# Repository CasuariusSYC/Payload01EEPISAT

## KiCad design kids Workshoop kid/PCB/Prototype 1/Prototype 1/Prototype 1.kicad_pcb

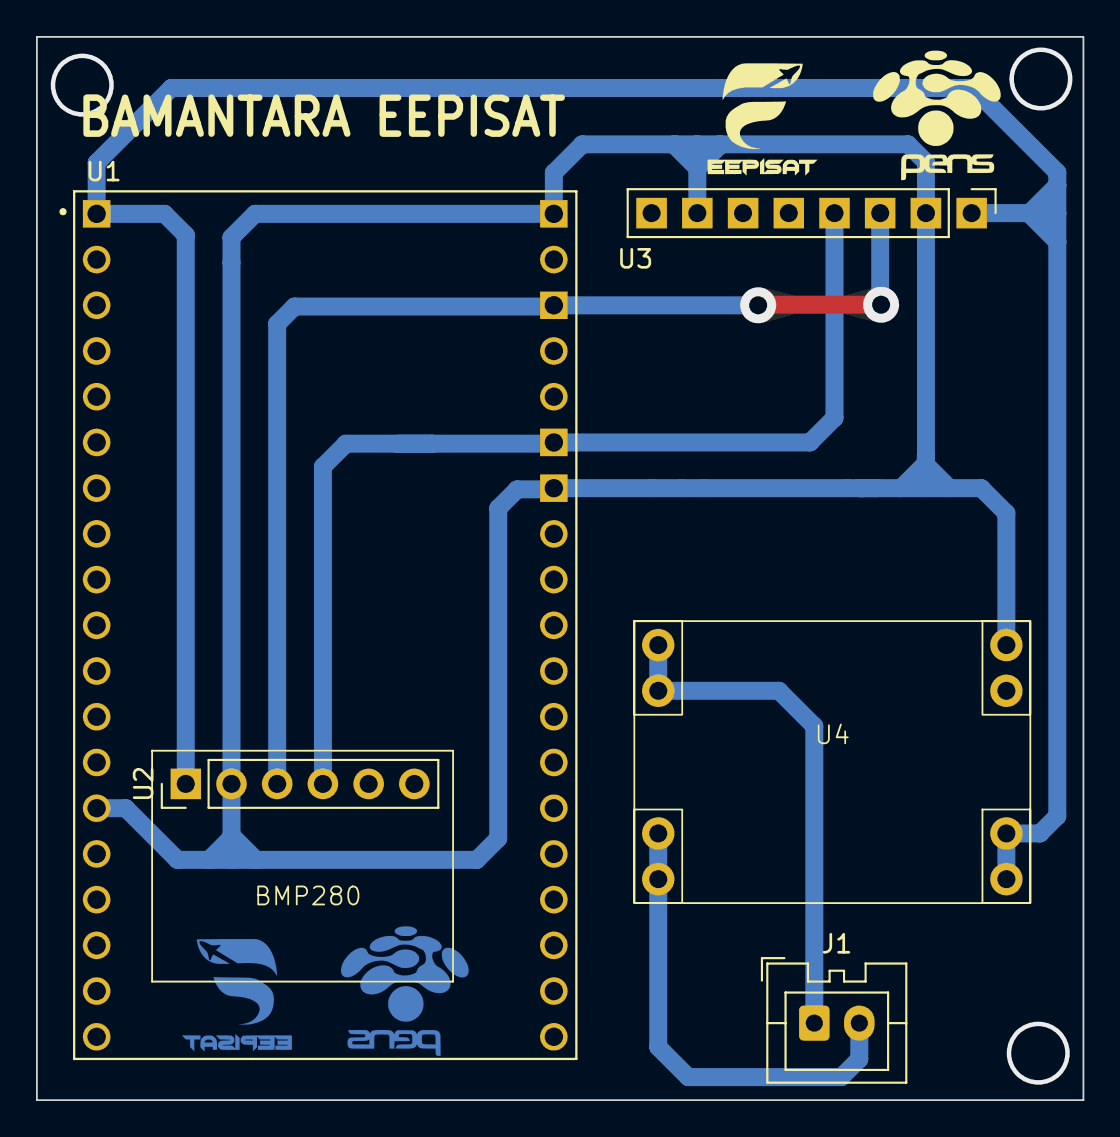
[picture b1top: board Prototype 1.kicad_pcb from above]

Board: 2 copper layers, 58.1 x 59.1 mm, 5 parts (0 on the bottom side), 6 nets.

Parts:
J1: Conn_01x02_Pin; JST_XA_B02B-XASK-1_1x02_P2.50mm_Vertical
U1: ESP32-DEVKITC-32U; MODULE_ESP32-DEVKITC-32U
U2: PinHeader_1x06_P2.54mm_Vertical
U3: PinHeader_1x08_P2.54mm_Vertical
U4: MP1584

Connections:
GND: U1.14 (GND1), U1.32 (GND2), U1.38 (GND3), U2.2 (GND), U3.2 (GND), U3.7 (AD0), U4.4 (OUT-)
unnamed: J1.1, U4.2 (IN-)
unnamed: J1.2, U4.1 (IN+)
SCL: U1.36 (IO22), U2.3 (SCL), U3.3 (SCL)
SDA: U1.33 (IO21), U2.4 (SDA), U3.4 (SDA)
VCC: U1.1 (3V3), U2.1 (VCC), U3.1 (VCC), U4.3 (OUT+)

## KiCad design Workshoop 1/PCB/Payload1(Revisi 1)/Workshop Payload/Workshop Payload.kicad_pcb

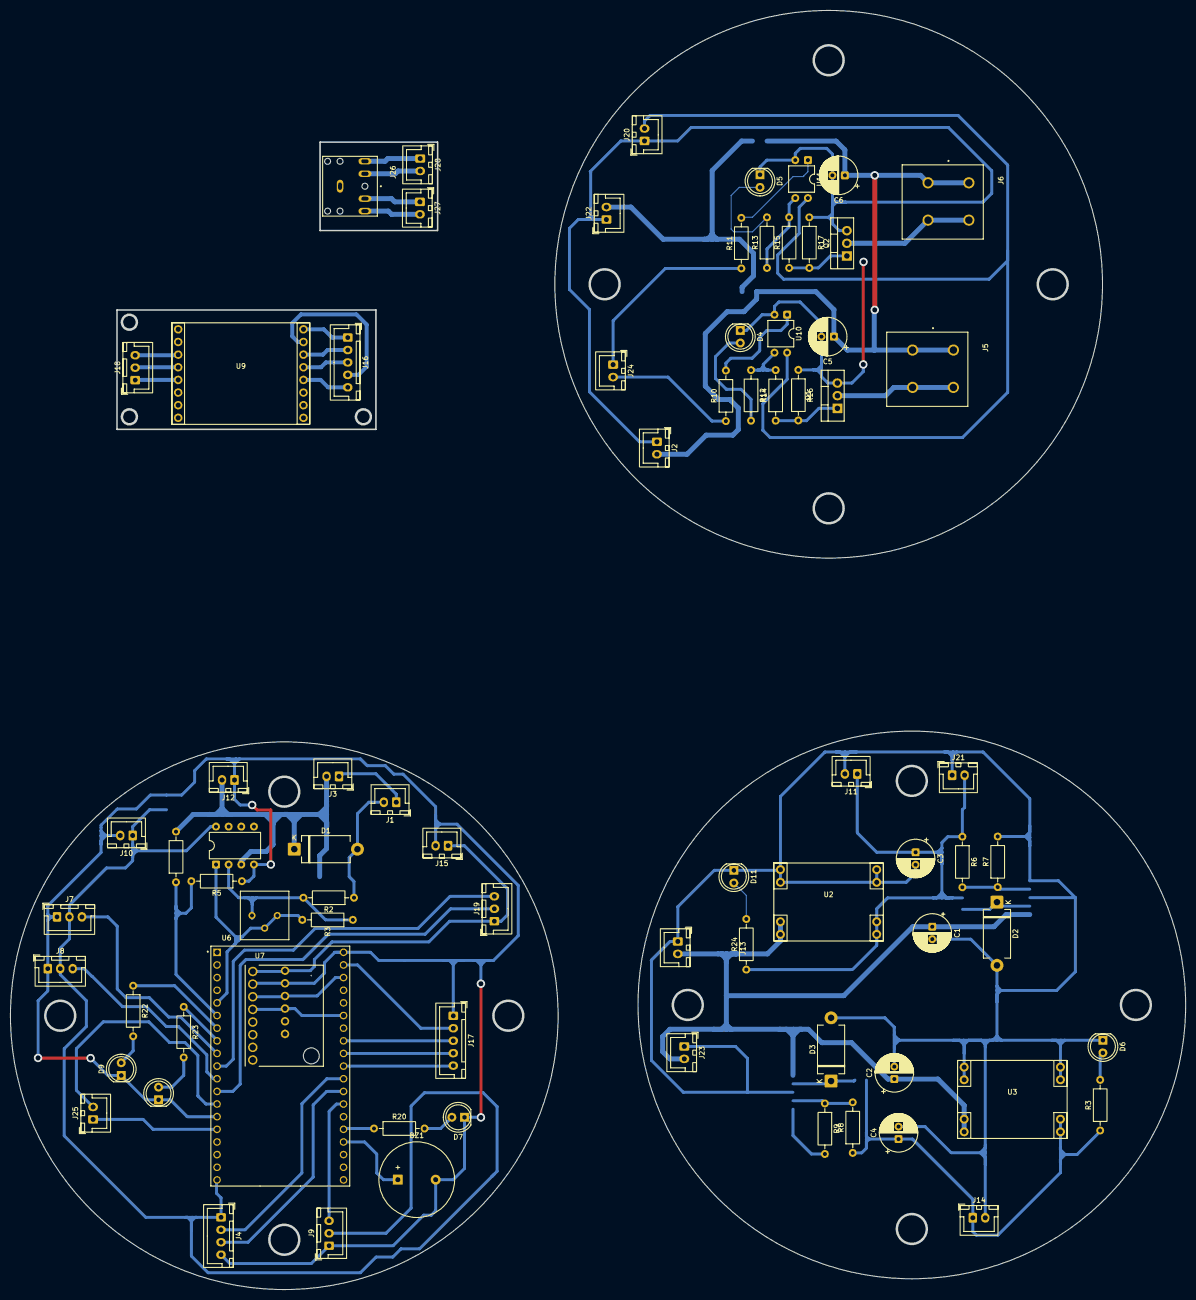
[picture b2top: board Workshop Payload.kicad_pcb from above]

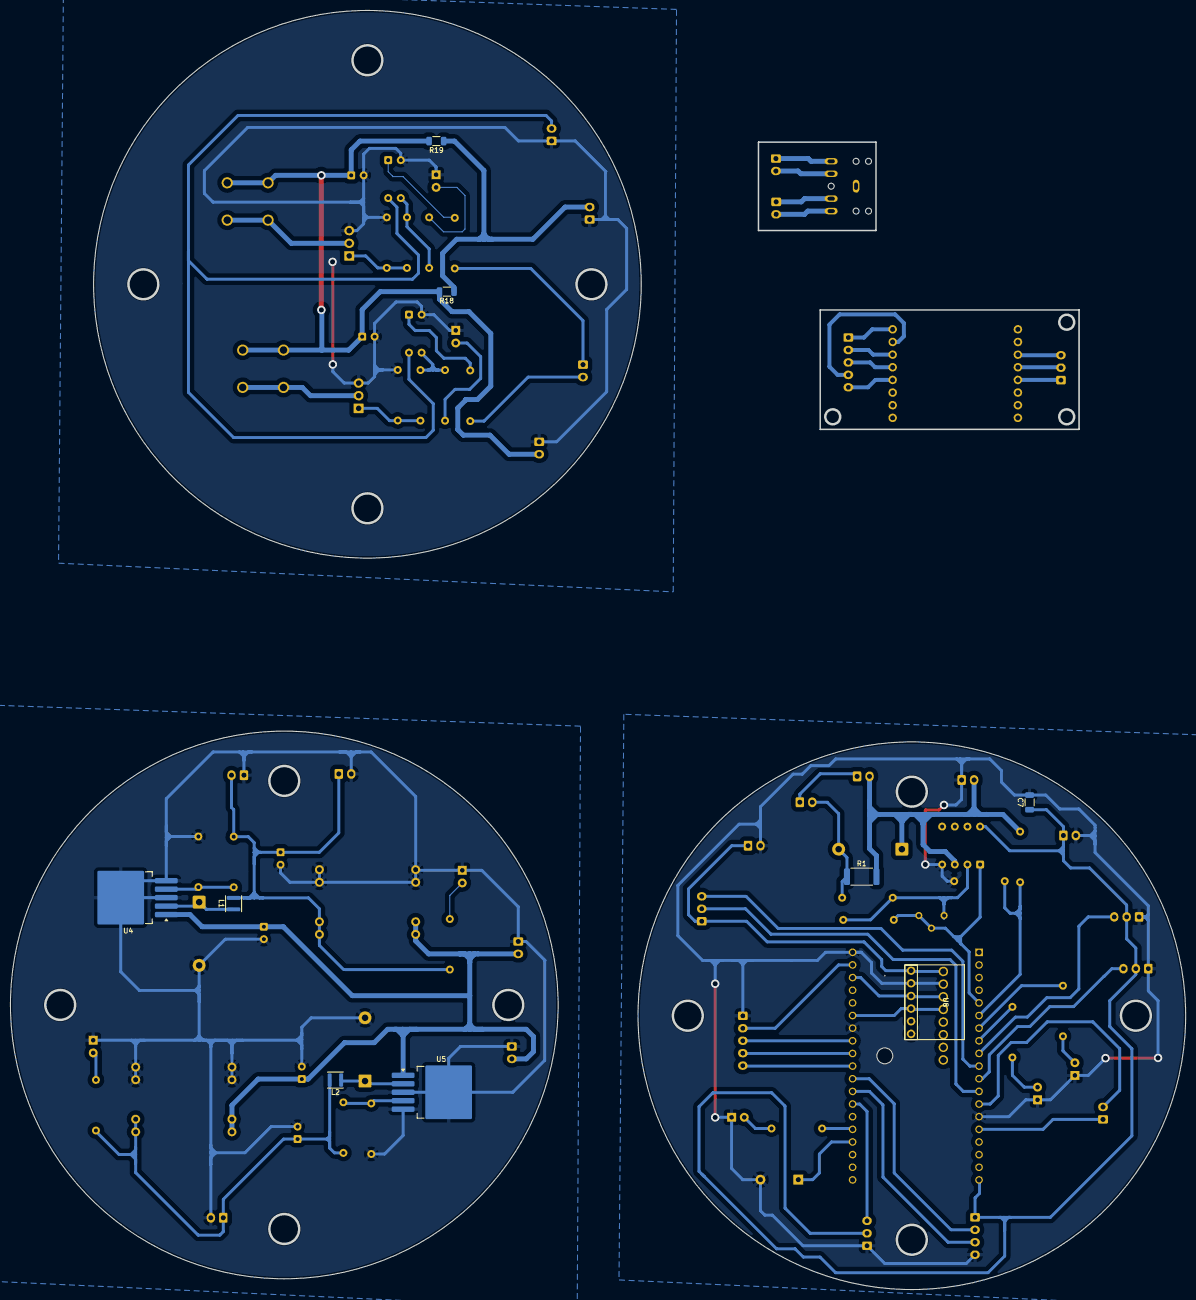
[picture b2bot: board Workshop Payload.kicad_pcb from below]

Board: 2 copper layers, 236.0 x 256.9 mm, 86 parts (9 on the bottom side), 62 nets.

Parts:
BZ1: Buzzer; Buzzer_15x7.5RM7.6
C1, C2: 470uF; CP_Radial_D7.5mm_P2.50mm
C3, C4: 220uF; CP_Radial_D7.5mm_P2.50mm
C5, C6: 100uF; CP_Radial_D7.5mm_P2.50mm
C7: 10uF; C_1206_3216Metric
D1: 1N4729A; D_DO-201_P12.70mm_Horizontal
D2, D3: 1N5822; D_DO-201_P12.70mm_Horizontal
D4, D5, D6, D7, D9, D10, D11: LED; LED_D5.0mm
J1: Battery; JST_XH_B2B-XH-A_1x02_P2.50mm_Vertical
J2: Backup Battery; JST_XH_B2B-XH-A_1x02_P2.50mm_Vertical
J3: RBF Switch; JST_XH_B2B-XH-A_1x02_P2.50mm_Vertical
J4: SAM-M10Q; JST_XH_B4B-XH-A_1x04_P2.50mm_Vertical
J5, J6: 2604-1302; WAGO_2604-1302
J7: Servo 1; JST_XH_B3B-XH-A_1x03_P2.50mm_Vertical
J8: Servo 2; JST_XH_B3B-XH-A_1x03_P2.50mm_Vertical
J9: Servo 3; JST_XH_B3B-XH-A_1x03_P2.50mm_Vertical
J10, J11: 5V; JST_XH_B2B-XH-A_1x02_P2.50mm_Vertical
J12, J13, J22, J23: 8.4V; JST_XH_B2B-XH-A_1x02_P2.50mm_Vertical
J14, J15: 3V3; JST_XH_B2B-XH-A_1x02_P2.50mm_Vertical
J16: Socket LoRa 2; JST_XH_B5B-XH-A_1x05_P2.50mm_Vertical
J17: Socket LoRa MCU 1; JST_XH_B5B-XH-A_1x05_P2.50mm_Vertical
J18: Socket LoRa 1; JST_XH_B3B-XH-A_1x03_P2.50mm_Vertical
J19: Socket LoRa MCU 2; JST_XH_B3B-XH-A_1x03_P2.50mm_Vertical
J20, J21: 5V Detonator; JST_XH_B2B-XH-A_1x02_P2.50mm_Vertical
J24, J25: Pin Detonator; JST_XH_B2B-XH-A_1x02_P2.50mm_Vertical
J26: SJ1-3525N; CUI_SJ1-3525N
J27: Kontak 2; JST_XH_B2B-XH-A_1x02_P2.50mm_Vertical
J28: Kontak 1; JST_XH_B2B-XH-A_1x02_P2.50mm_Vertical
L1, L2: 68uH; L_APV_ANR3015
Q1, Q2: IRLZ44N; TO-220-3_Vertical
R1: 0.1; R_2512_6332Metric
R2, R16, R17: 10k; R_Axial_DIN0207_L6.3mm_D2.5mm_P10.16mm_Horizontal
R3, R4, R5, R7, R9: 1k; R_Axial_DIN0207_L6.3mm_D2.5mm_P10.16mm_Horizontal
R3#2, R12, R13, R20, R22, R23: 220; R_Axial_DIN0207_L6.3mm_D2.5mm_P10.16mm_Horizontal
R6: 3.3k; R_Axial_DIN0207_L6.3mm_D2.5mm_P10.16mm_Horizontal
R8: 1.8k; R_Axial_DIN0207_L6.3mm_D2.5mm_P10.16mm_Horizontal
R10, R11: 100; R_Axial_DIN0207_L6.3mm_D2.5mm_P10.16mm_Horizontal
R14, R15: 20k; R_Axial_DIN0207_L6.3mm_D2.5mm_P10.16mm_Horizontal
R18, R19: 0; R_1206_3216Metric
R24: 680; R_Axial_DIN0207_L6.3mm_D2.5mm_P10.16mm_Horizontal
RV1: R_Potentiometer_Trim; Potentiometer_Bourns_3386P_Vertical
U1: LM358; DIP-8_W7.62mm
U2, U3: MP1584
U4, U5: LM2596S-ADJ; TO-263-5_TabPin3
U6: ESP32-DEVKITC-32U; MODULE_ESP32-DEVKITC-32U
U7: GY-521; MODULE_GY-521
U8: BMP280
U9: LoRa Ra-02 SX1278
U10, U11: PC817; DIP-4_W7.62mm

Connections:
+3V3: C4.1, J14.1, J15.1, J19.1, L2.2, R3#2.1, R8.1, U3.3 (OUT+), U7.VCC, U8.1 (VCC)
+5V: C3.1, C7.1, J4.1, J7.2, J8.2, J9.2, J10.1, J11.1, J20.2, J21.2, L1.2, R6.1, R24.1, U1.8 (V+), U2.3 (OUT+), U6.19 (EXT_5V), U10.4, U11.4
+BATT: J1.1, J3.1
ADC 1: R3.2, RV1.2, RV1.3, U1.1, U6.5 (IO34)
ADC 2: R4.1, R5.2, U6.6 (IO35)
BUZZER: BZ1.1 (+), U6.23 (IO15)
Backup: C5.1, C6.1, J2.2, J5.1_1 (1), J5.1_2 (1), J6.1_1 (1), J6.1_2 (1), R18.2, R19.2
D100: J19.3, U6.10 (IO26)
DETONATOR 1: J25.2, U6.13 (IO12)
DETONATOR 2: J25.1, U6.15 (IO13)
GND: BZ1.2 (-), C1.2, C2.2, C3.2, C4.2, C5.2, C6.2, C7.2, D2.2 (A), D3.2 (A), D4.1 (K), D5.1 (K), D6.1 (K), D7.1 (K), D9.1 (K), D10.1 (K), D11.1 (K), J2.1, J4.4, J7.1, J8.1, J9.1, J10.2, J11.2, J12.1, J13.1, J14.2, J15.2, J17.1, J20.1, J21.1, J22.1, J23.1, Q1.3 (S), Q2.3 (S), R5.1, R7.2, R9.2, R16.1, R17.1, U1.4 (V-), U2.2 (IN-), U2.4 (OUT-), U3.2 (IN-), U3.4 (OUT-), U4.3 (GND), U4.5 (~ON/OFF), U5.3 (GND), U5.5 (~ON/OFF), U6.14 (GND1), U6.32 (GND2), U6.38 (GND3), U7.GND, U8.2 (GND), U10.2, U11.2
GND2: D1.2 (A), J1.2, R1.1, R2.1
LED1: R20.1, U6.24 (IO2)
LED3: R22.1, U6.7 (IO32)
LED4: R23.1, U6.8 (IO33)
MISO: J17.3, U6.31 (IO19)
MOSI: J17.2, U6.37 (IO23)
NSS: J17.5, U6.29 (IO5)
unnamed: D2.1 (K), L1.1, U4.2 (OUT)
unnamed: D3.1 (K), L2.1, U5.2 (OUT)
unnamed: D4.2 (A), R12.2
unnamed: D5.2 (A), R13.2
unnamed: D6.2 (A), R3#2.2
unnamed: D7.2 (A), R20.2
unnamed: D9.2 (A), R22.2
unnamed: D10.2 (A), R23.2
unnamed: D11.2 (A), R24.2
unnamed: J16.1, U9.9 (GND)
unnamed: J16.2, U9.11 (MOSI)
unnamed: J16.3, U9.12 (MISO)
unnamed: J16.4, U9.10 (NSS)
unnamed: J16.5, U9.13 (SCK)
unnamed: J18.1, U9.5 (D100)
unnamed: J18.2, U9.4 (RST)
unnamed: J18.3, U9.3 (3V3)
unnamed: J26.10, J27.1
unnamed: J26.2, J27.2
unnamed: J26.3, J28.1
unnamed: J26.11, J28.2
unnamed: J5.2_1 (2), J5.2_2 (2), Q1.2 (D)
unnamed: Q1.1 (G), R14.1, R16.2
unnamed: J6.2_1 (2), J6.2_2 (2), Q2.2 (D)
unnamed: Q2.1 (G), R15.1, R17.2
unnamed: R10.2, U10.1
unnamed: R11.2, U11.1
unnamed: R12.1, R14.2, U10.3
unnamed: R13.1, R15.2, U11.3
unnamed: R2.2, R3.1, RV1.1, U1.2 (-)
unnamed: R6.2, R7.1, U4.4 (FB)
unnamed: R8.2, R9.1, U5.4 (FB)
OUTSW: C1.1, C2.1, D1.1 (K), J3.2, J12.2, J13.2, J22.2, J23.2, R1.2, R4.2, R18.1, R19.1, U1.3 (+), U2.1 (IN+), U3.1 (IN+), U4.1 (VIN), U5.1 (VIN)
RST: J19.2, U6.12 (IO14)
RX2_ESP: J4.3, U6.27 (IO16)
SCK: J17.4, U6.30 (IO18)
SCL: U6.36 (IO22), U7.SCL, U8.3 (SCL)
SDA: U6.33 (IO21), U7.SDA, U8.4 (SDA)
SERVO 1: J7.3, U6.9 (IO25)
SERVO 2: J8.3, U6.11 (IO27)
SERVO 3: J9.3, U6.26 (IO4)
TX2_ESP: J4.2, U6.28 (IO17)
cDETONATOR 1: J24.2, R10.1
cDETONATOR 2: J24.1, R11.1

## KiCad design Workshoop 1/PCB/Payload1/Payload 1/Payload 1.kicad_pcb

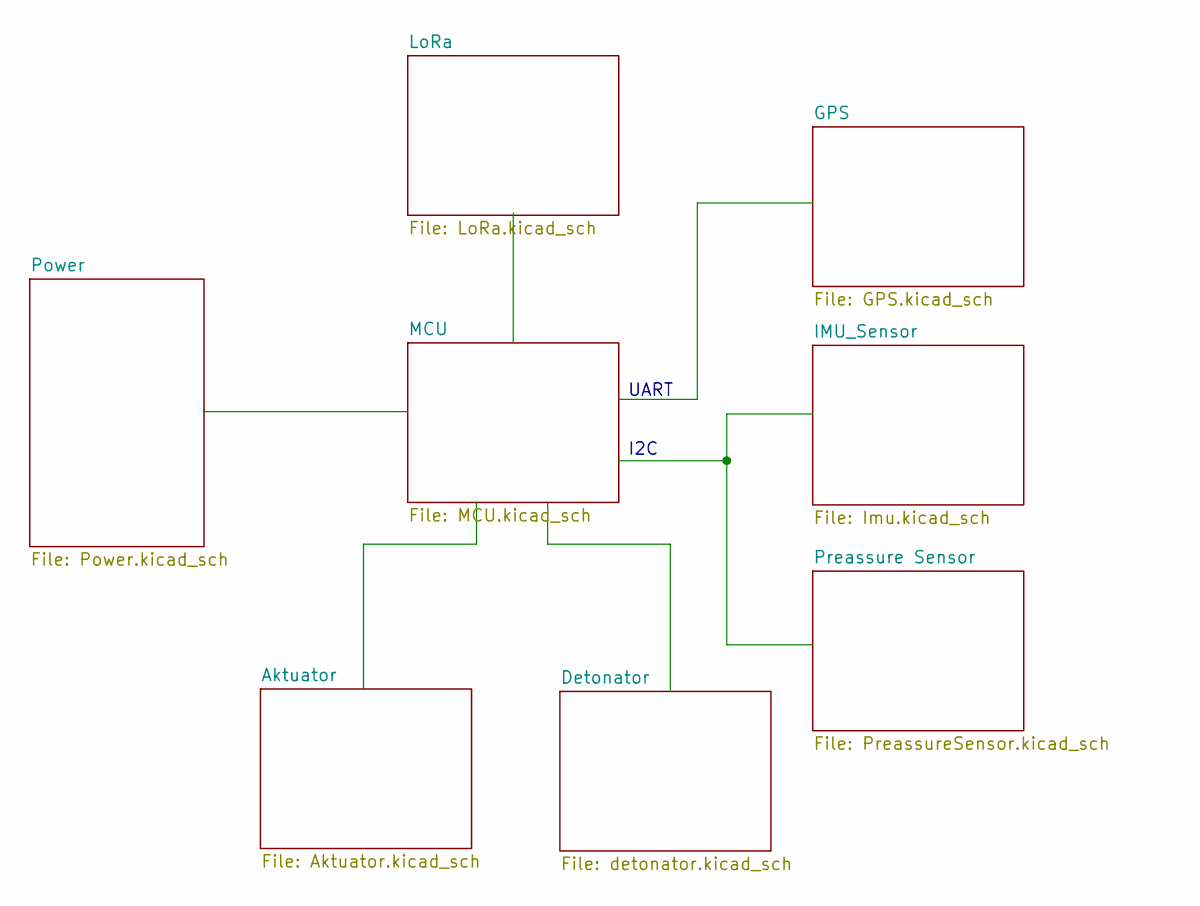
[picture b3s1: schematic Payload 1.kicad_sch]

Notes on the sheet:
I2C
UART

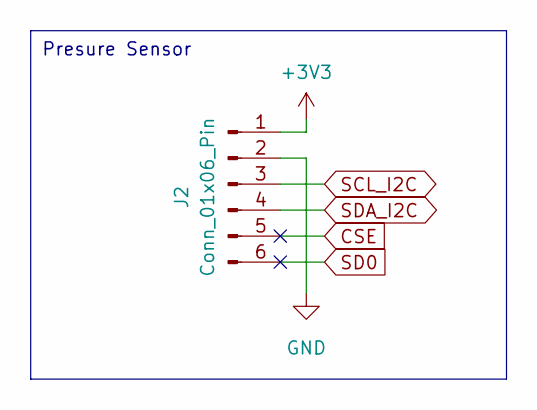
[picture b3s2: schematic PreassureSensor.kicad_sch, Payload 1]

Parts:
J2: Conn_01x06_Pin; PinHeader_1x06_P2.54mm_Vertical

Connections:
+3V3: J2.1; also elsewhere on the board
CSE: J2.5
GND: J2.2; also elsewhere on the board
SCL_I2C: J2.3; also elsewhere on the board
SD0: J2.6
SDA_I2C: J2.4; also elsewhere on the board

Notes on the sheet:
Presure Sensor

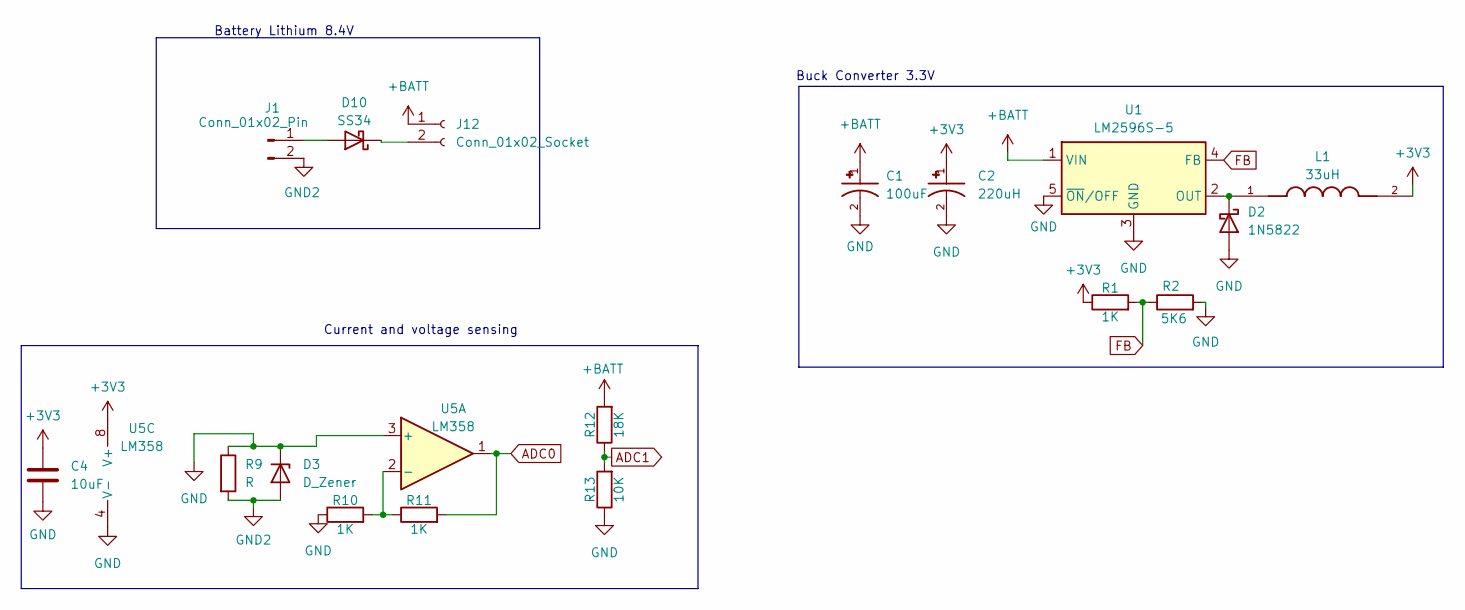
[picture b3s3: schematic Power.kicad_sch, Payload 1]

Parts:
C1: 100uF; CAP_EEEFN1H101L; PARTREV 10-Oct-19
C2: 220uH; CAP_EEEFN1V221V; PARTREV 10-Oct-19
C4: 10uF; C_0805_2012Metric_Pad1.18x1.45mm_HandSolder
D2: 1N5822; D_DO-201AD_P15.24mm_Horizontal
D3: D_Zener; D_0805_2012Metric_Pad1.15x1.40mm_HandSolder
D10: SS34; D_SMA_Handsoldering
J1: Conn_01x02_Pin; JST_EH_B2B-EH-A_1x02_P2.50mm_Vertical
J12: Conn_01x02_Socket; JST_EH_B2B-EH-A_1x02_P2.50mm_Vertical
L1: 33uH; IND_ETQP4M330YFN; PARTREV 1-Feb-20
R1, R10, R11: 1K; R_0805_2012Metric_Pad1.20x1.40mm_HandSolder
R2: 5K6; R_0805_2012Metric_Pad1.20x1.40mm_HandSolder
R9: R; R_2512_6332Metric_Pad1.40x3.35mm_HandSolder
R12: 18K; R_0805_2012Metric_Pad1.20x1.40mm_HandSolder
R13: 10K; R_0805_2012Metric_Pad1.20x1.40mm_HandSolder
U1: LM2596S-5; TO-263-5_TabPin3
U5: LM358; MSOP-8_3x3mm_P0.65mm

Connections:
+3V3: C2.1, C4.1, L1.2, R1.1, U5.8 (V+); also elsewhere on the board
+BATT: C1.1, J12.1, R12.2, U1.1 (VIN)
ADC0: R11.2, U5.1; also elsewhere on the board
ADC1: R12.1, R13.2; also elsewhere on the board
FB: R1.2, R2.1, U1.4 (FB)
GND: C1.2, C2.2, C4.2, D2.2 (A), D3.1 (K), R2.2, R9.1, R10.1, R13.1, U1.3 (GND), U1.5 (~ON/OFF), U5.3 (+), U5.4 (V-); also elsewhere on the board
GND2: D3.2 (A), J1.2, R9.2
unnamed: D2.1 (K), L1.1, U1.2 (OUT)
unnamed: D10.2 (A), J1.1
unnamed: D10.1 (K), J12.2
unnamed: R10.2, R11.1, U5.2 (-)

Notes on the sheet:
Battery Lithium 8.4V
Current and voltage sensing
Buck Converter 3.3V

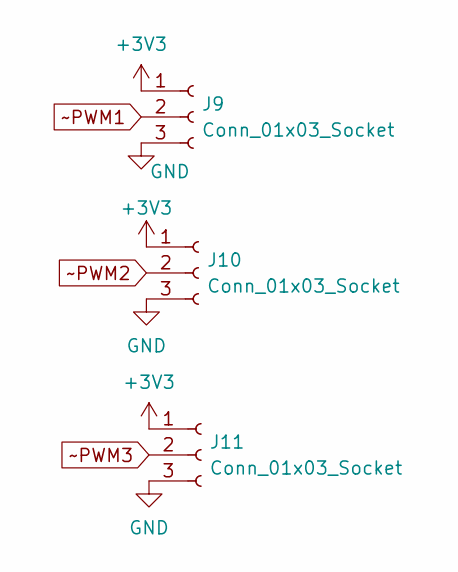
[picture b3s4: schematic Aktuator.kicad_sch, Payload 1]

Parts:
J9, J10, J11: Conn_01x03_Socket; JST_EH_B3B-EH-A_1x03_P2.50mm_Vertical

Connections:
+3V3: J9.1, J10.1, J11.1; also elsewhere on the board
GND: J9.3, J10.3, J11.3; also elsewhere on the board
~PWM1: J9.2; also elsewhere on the board
~PWM2: J10.2; also elsewhere on the board
~PWM3: J11.2; also elsewhere on the board

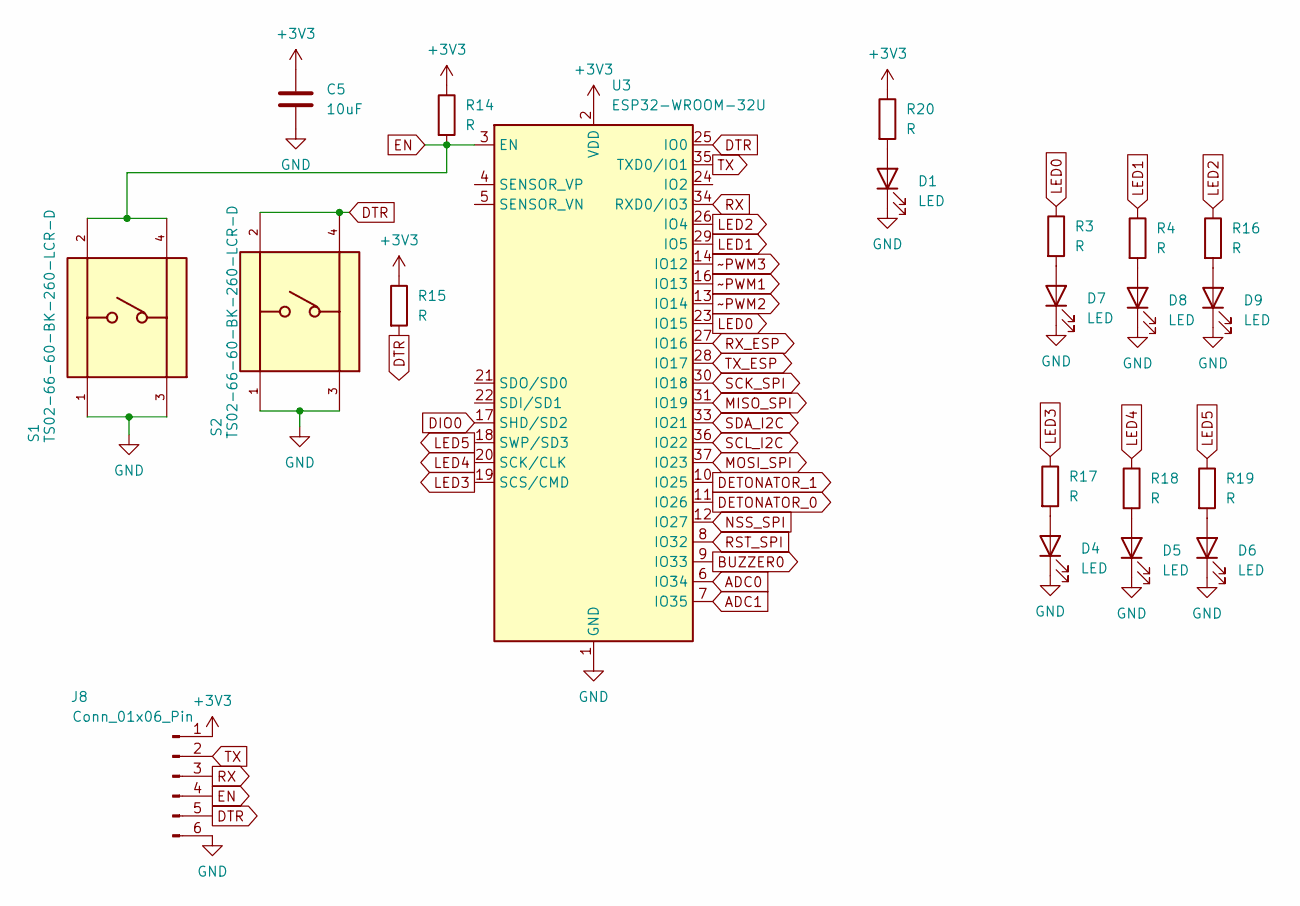
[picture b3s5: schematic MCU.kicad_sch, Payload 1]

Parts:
C5: 10uF; C_0805_2012Metric_Pad1.18x1.45mm_HandSolder
D1, D4, D5, D6, D7, D8, D9: LED; LED_0805_2012Metric_Pad1.15x1.40mm_HandSolder
J8: Conn_01x06_Pin; PinHeader_1x06_P2.54mm_Vertical
R3, R4, R14, R15, R16, R17, R18, R19, R20: R; R_0805_2012Metric_Pad1.20x1.40mm_HandSolder
S1, S2: TS02-66-60-BK-260-LCR-D; SW_TS02-66-60-BK-260-LCR-D; PARTREV 1.0
U3: ESP32-WROOM-32U

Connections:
+3V3: C5.1, J8.1, R14.1, R15.1, R20.1, U3.2 (VDD); also elsewhere on the board
ADC0: U3.6 (IO34); also elsewhere on the board
ADC1: U3.7 (IO35); also elsewhere on the board
BUZZER0: U3.9 (IO33)
DETONATOR_0: U3.11 (IO26); also elsewhere on the board
DETONATOR_1: U3.10 (IO25); also elsewhere on the board
DIO0: U3.17 (SHD/SD2)
DTR: J8.5, R15.2, S2.2, S2.4, U3.25 (IO0)
EN: J8.4, R14.2, S1.2, S1.4, U3.3 (EN)
GND: C5.2, D1.1 (K), D4.1 (K), D5.1 (K), D6.1 (K), D7.1 (K), D8.1 (K), D9.1 (K), J8.6, S1.1, S1.3, S2.1, S2.3, U3.1 (GND), U3.15 (GND), U3.38 (GND), U3.39 (GND); also elsewhere on the board
LED0: R3.1, U3.23 (IO15)
LED1: R4.1, U3.29 (IO5)
LED2: R16.1, U3.26 (IO4)
LED3: R17.1, U3.19 (SCS/CMD)
LED4: R18.1, U3.20 (SCK/CLK)
LED5: R19.1, U3.18 (SWP/SD3)
MISO_SPI: U3.31 (IO19); also elsewhere on the board
MOSI_SPI: U3.37 (IO23); also elsewhere on the board
NSS_SPI: U3.12 (IO27); also elsewhere on the board
unnamed: D1.2 (A), R20.2
unnamed: D4.2 (A), R17.2
unnamed: D5.2 (A), R18.2
unnamed: D6.2 (A), R19.2
unnamed: D7.2 (A), R3.2
unnamed: D8.2 (A), R4.2
unnamed: D9.2 (A), R16.2
RST_SPI: U3.8 (IO32); also elsewhere on the board
RX: J8.3, U3.34 (RXD0/IO3)
RX_ESP: U3.27 (IO16); also elsewhere on the board
SCK_SPI: U3.30 (IO18); also elsewhere on the board
SCL_I2C: U3.36 (IO22); also elsewhere on the board
SDA_I2C: U3.33 (IO21); also elsewhere on the board
TX: J8.2, U3.35 (TXD0/IO1)
TX_ESP: U3.28 (IO17); also elsewhere on the board
~PWM1: U3.16 (IO13); also elsewhere on the board
~PWM2: U3.13 (IO14); also elsewhere on the board
~PWM3: U3.14 (IO12); also elsewhere on the board

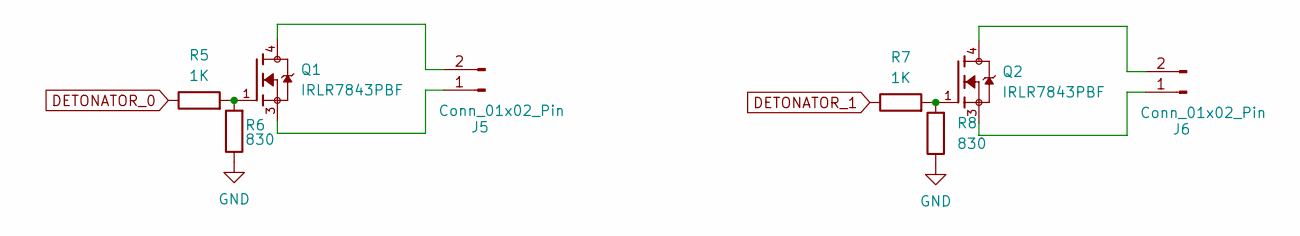
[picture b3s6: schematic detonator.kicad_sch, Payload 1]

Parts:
J5, J6: Conn_01x02_Pin; JST_EH_B2B-EH-A_1x02_P2.50mm_Vertical
Q1, Q2: IRLR7843PBF; TO229P990X239-3_4N; PARTREV 06
R5, R7: 1K; R_0805_2012Metric_Pad1.20x1.40mm_HandSolder
R6, R8: 830; R_0805_2012Metric_Pad1.20x1.40mm_HandSolder

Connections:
DETONATOR_0: R5.1; also elsewhere on the board
DETONATOR_1: R7.1; also elsewhere on the board
GND: R6.1, R8.1; also elsewhere on the board
unnamed: J5.1, Q1.3
unnamed: J5.2, Q1.4
unnamed: J6.1, Q2.3
unnamed: J6.2, Q2.4
unnamed: Q1.1, R5.2, R6.2
unnamed: Q2.1, R7.2, R8.2

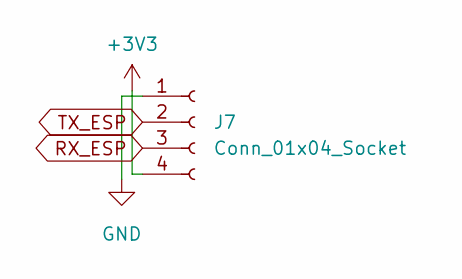
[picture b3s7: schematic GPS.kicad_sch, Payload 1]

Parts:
J7: Conn_01x04_Socket; JST_EH_B4B-EH-A_1x04_P2.50mm_Vertical

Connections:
+3V3: J7.4; also elsewhere on the board
GND: J7.1; also elsewhere on the board
RX_ESP: J7.3; also elsewhere on the board
TX_ESP: J7.2; also elsewhere on the board

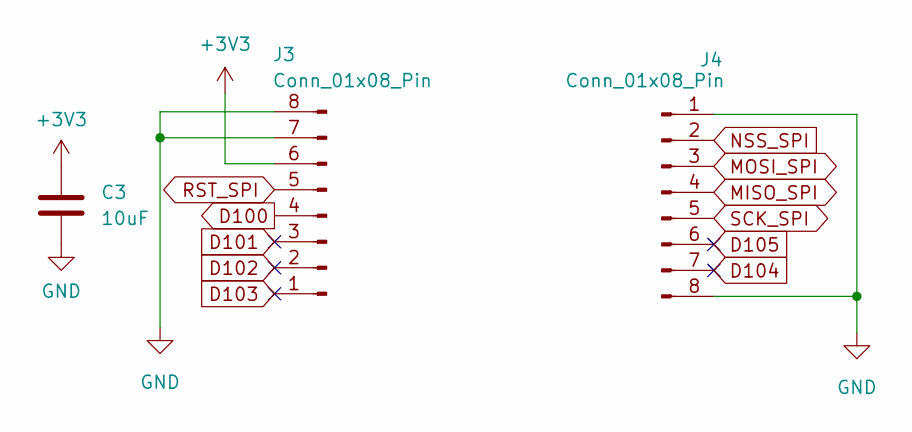
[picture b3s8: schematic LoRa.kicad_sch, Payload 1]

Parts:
C3: 10uF; C_0805_2012Metric_Pad1.18x1.45mm_HandSolder
J3, J4: Conn_01x08_Pin; PinHeader_1x08_P2.54mm_Vertical

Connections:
+3V3: C3.1, J3.6; also elsewhere on the board
D100: J3.4
D101: J3.3
D102: J3.2
D103: J3.1
D104: J4.7
D105: J4.6
GND: C3.2, J3.7, J3.8, J4.1, J4.8; also elsewhere on the board
MISO_SPI: J4.4; also elsewhere on the board
MOSI_SPI: J4.3; also elsewhere on the board
NSS_SPI: J4.2; also elsewhere on the board
RST_SPI: J3.5; also elsewhere on the board
SCK_SPI: J4.5; also elsewhere on the board

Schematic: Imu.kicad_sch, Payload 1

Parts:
U4: GY-521; MODULE_GY-521; PARTREV NA

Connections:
+3V3: U4.VCC; also elsewhere on the board
GND: U4.AD0, U4.GND; also elsewhere on the board
SCL_I2C: U4.SCL; also elsewhere on the board
SDA_I2C: U4.SDA; also elsewhere on the board

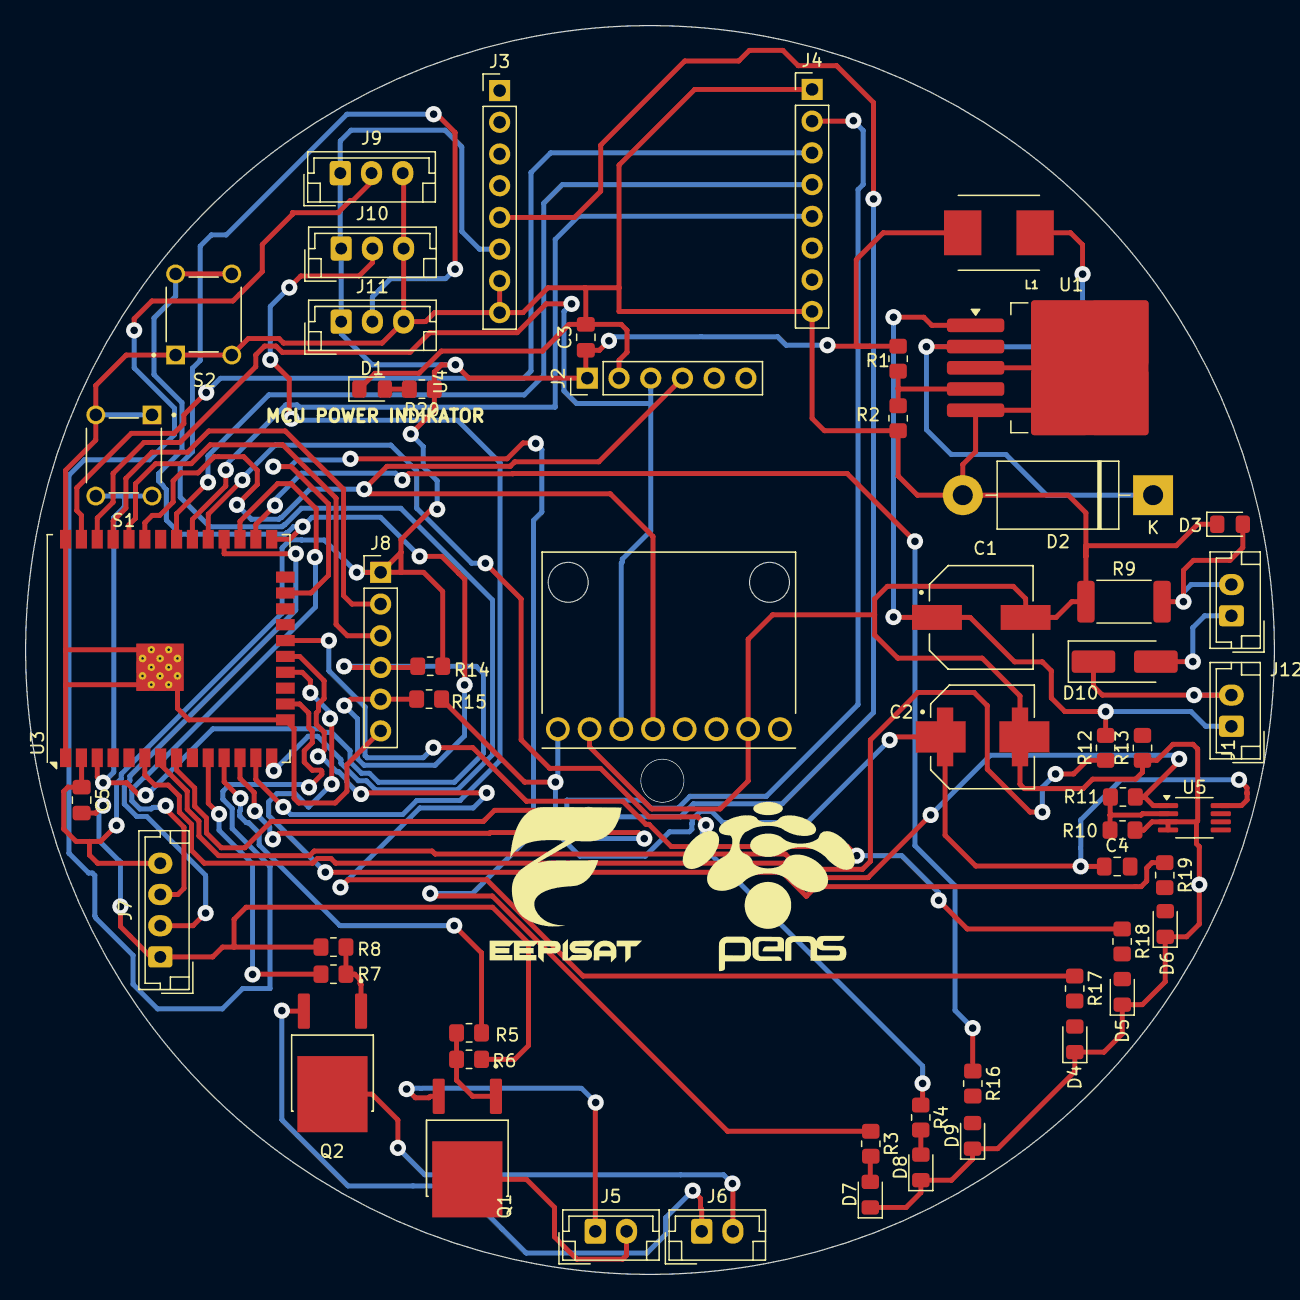
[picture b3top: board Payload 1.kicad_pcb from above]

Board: 2 copper layers, 100.0 x 100.0 mm, 56 parts (0 on the bottom side), 48 nets.

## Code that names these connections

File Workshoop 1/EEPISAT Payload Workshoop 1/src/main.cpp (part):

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// // ---------- 1.2 Pin ESP32 ----------
// const int PIN_DETONATOR1 = 2;
// const int PIN_DETONATOR2 = 32;
// const int PIN_LED1 = 25;   // MPU6050: ON kalau OK, KEDIP kalau error
// const int PIN_LED2 = 27;   // BMP280 : ON kalau OK, KEDIP kalau error
// const int PIN_LED3 = 33;   // LoRa   : ON kalau OK, KEDIP kalau error
// const int PIN_GPS_RX = 16;
// const int PIN_GPS_TX = 17;
// const int PIN_LORA_SCK  = 18;
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
// void updateLedIndicators() {
//   if (mpuOK) {
//     digitalWrite(PIN_LED1, HIGH);
//   } else {
//     blinkStep(PIN_LED1, LED_ERROR_BLINK_MS);
//   }

//   if (bmpOK) {
//     digitalWrite(PIN_LED2, HIGH);
//   } else {
//     blinkStep(PIN_LED2, LED_ERROR_BLINK_MS);
//   }

//   if (loraOK) {
//     digitalWrite(PIN_LED3, HIGH);
//   } else {
//     blinkStep(PIN_LED3, LED_ERROR_BLINK_MS);
//   }
// }

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// void errorHalt(const char* pesan) {
//   Serial.println(pesan);
//   while (1) {
//     digitalWrite(PIN_LED1, !digitalRead(PIN_LED1));
//     digitalWrite(PIN_LED2, !digitalRead(PIN_LED2));
//     digitalWrite(PIN_LED3, !digitalRead(PIN_LED3));
//     delay(200);
//   }
// }
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//   Serial.println("Kalibrasi gyro... JANGAN GERAKKAN SENSOR!");

//   for (int i = 0; i < 40; i++) {
//     blinkStep(PIN_LED1, 100);
//     delay(50);
//   }

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//   int n = 0;

//   for (int i = 0; i < JUMLAH_SAMPEL_GYRO; i++) {
//     blinkStep(PIN_LED1, 100);
//     int16_t ax, ay, az, gx, gy, gz;
//     if (mpuReadRaw(ax, ay, az, gx, gy, gz)) {
//       tx += gx / MPU6050_GYRO_SCALE;
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
//   if (n == 0) {
//     mpuOK = false;
//     ledOff(PIN_LED1);
//     failLembut("Gagal baca MPU6050 saat kalibrasi - lanjut tanpa IMU");
//     return;
//   }
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//   Serial.println("Kalibrasi tekanan udara... jangan pindahkan payload!");

//   for (int i = 0; i < 30; i++) {
//     blinkStep(PIN_LED2, 100);
//     bmp.readPressure();
//     delay(70);
//   }

//   double total = 0;
//   for (int i = 0; i < JUMLAH_SAMPEL_TEKANAN; i++) {
//     blinkStep(PIN_LED2, 100);
//     total += bmp.readPressure();
//     delay(70);
//   }
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// void setup() {
//   pinMode(PIN_DETONATOR1, OUTPUT); digitalWrite(PIN_DETONATOR1, LOW);
//   pinMode(PIN_DETONATOR2, OUTPUT); digitalWrite(PIN_DETONATOR2, LOW);
//   pinMode(PIN_LED1, OUTPUT);       digitalWrite(PIN_LED1, LOW);
//   pinMode(PIN_LED2, OUTPUT);       digitalWrite(PIN_LED2, LOW);
//   pinMode(PIN_LED3, OUTPUT);       digitalWrite(PIN_LED3, LOW);

//   Serial.begin(115200);
//   delay(100);
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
